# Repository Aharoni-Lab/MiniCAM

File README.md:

# MiniCAM
The MiniCAM is an open-source behaviroal camera for imaging freely behaving animals in behavioral and neuroscience experiments. The goal of the MiniCAM project is to provide an open-source, customizable, high-quality, and affordable alternative to using webcams or scientific USB cameras for behavioral imaging. The MiniCAM is powered and communicates over any commercial 50ohm coaxial cable minimizing the cabling that needs to run into the experimental environment. The coaxial cable connects the MiniDAQ to any version of UCLA Miniscope DAQs or MiniDAQs which then connects over USB3 to a host computer.

Using the [Miniscope Software](https://github.com/Aharoni-Lab/Miniscope-DAQ-QT-Software), multiple Miniscopes and MiniCAMs can be connected, streamed, and time-sync'ed recording simultaniously.

## MiniCAM Components
The MiniCAM consists of a custom printed circuit board (PCB), a 3D printed housing, an off the shelf M12 lens mount, a M12 camera lens, and an optional LED illumination ring. The PCB contains a 5MP CMOS image sensor, support electronics to power and serialize the imaging data, and an SMA coax connector. The image sensor can be configured through the Miniscope software and the optional LED illumination ring intensity can also be controlled through software. The MiniCAM runs at 50fps with 1024X768 resolution as the default configuration. Higher frame rate can be achieved by choosing smaller resolutions and higher resolution comes with lower frame rate.

## System Layout
The MiniCAM requires a UCLA Miniscope Data Acquisition (DAQ) board (connected over a 50ohm coaxial cable) and a host computer (connected over USB3) running the [Miniscope Software](https://github.com/Aharoni-Lab/Miniscope-DAQ-QT-Software) (or other third-party application that can stream UVC cameras and can communicate through a Miniscope DAQ). You can use any generation of Miniscope DAQ but you must update it with [the newest firmware](https://github.com/Aharoni-Lab/Miniscope-DAQ-Cypress-firmware). You can also use the cheaper and smaller version of the Miniscope DAQ called the MiniDAQ (open-source link coming soon). Once updated to the newest firmware, any Miniscope DAQ device will work with all Miniscope and MiniCAM devices. 

## M12 lenses and Coaxial Cables
Just like Miniscopes, the MiniCAM uses a 50Ohm coaxial cable for power, communication, and data. Any 50Ohm coax cable should work with the system. 

### M12 lenses
M12 lenses and M12 Mount Lens Holders are avaiable in Amazon (can be purchased at other places too). It can be handy to buy a M12 Lens Kit that comes with a range of M12 lenses for different view angles. We have been happy with the Arducam lens set which can be found on Amazon. If you are using the optional LED illumination ring or other nIR light source make sure to remove any IR filter located in the lens if applicable.

### Coaxial Cables
Any 50Ohm coaxial cable should be compatible with this system. It is not necessary to use the expensive, thin, flexible coax cables generally used with Miniscopes. The thicker the cable the longer length you can run (maxing out at around 10 to 15 meters). It generally is most convinient to get a coax cable with male SMA connectors on both ends to connect between the MiniCAM and MiniDAQ (or standard Miniscope DAQ).

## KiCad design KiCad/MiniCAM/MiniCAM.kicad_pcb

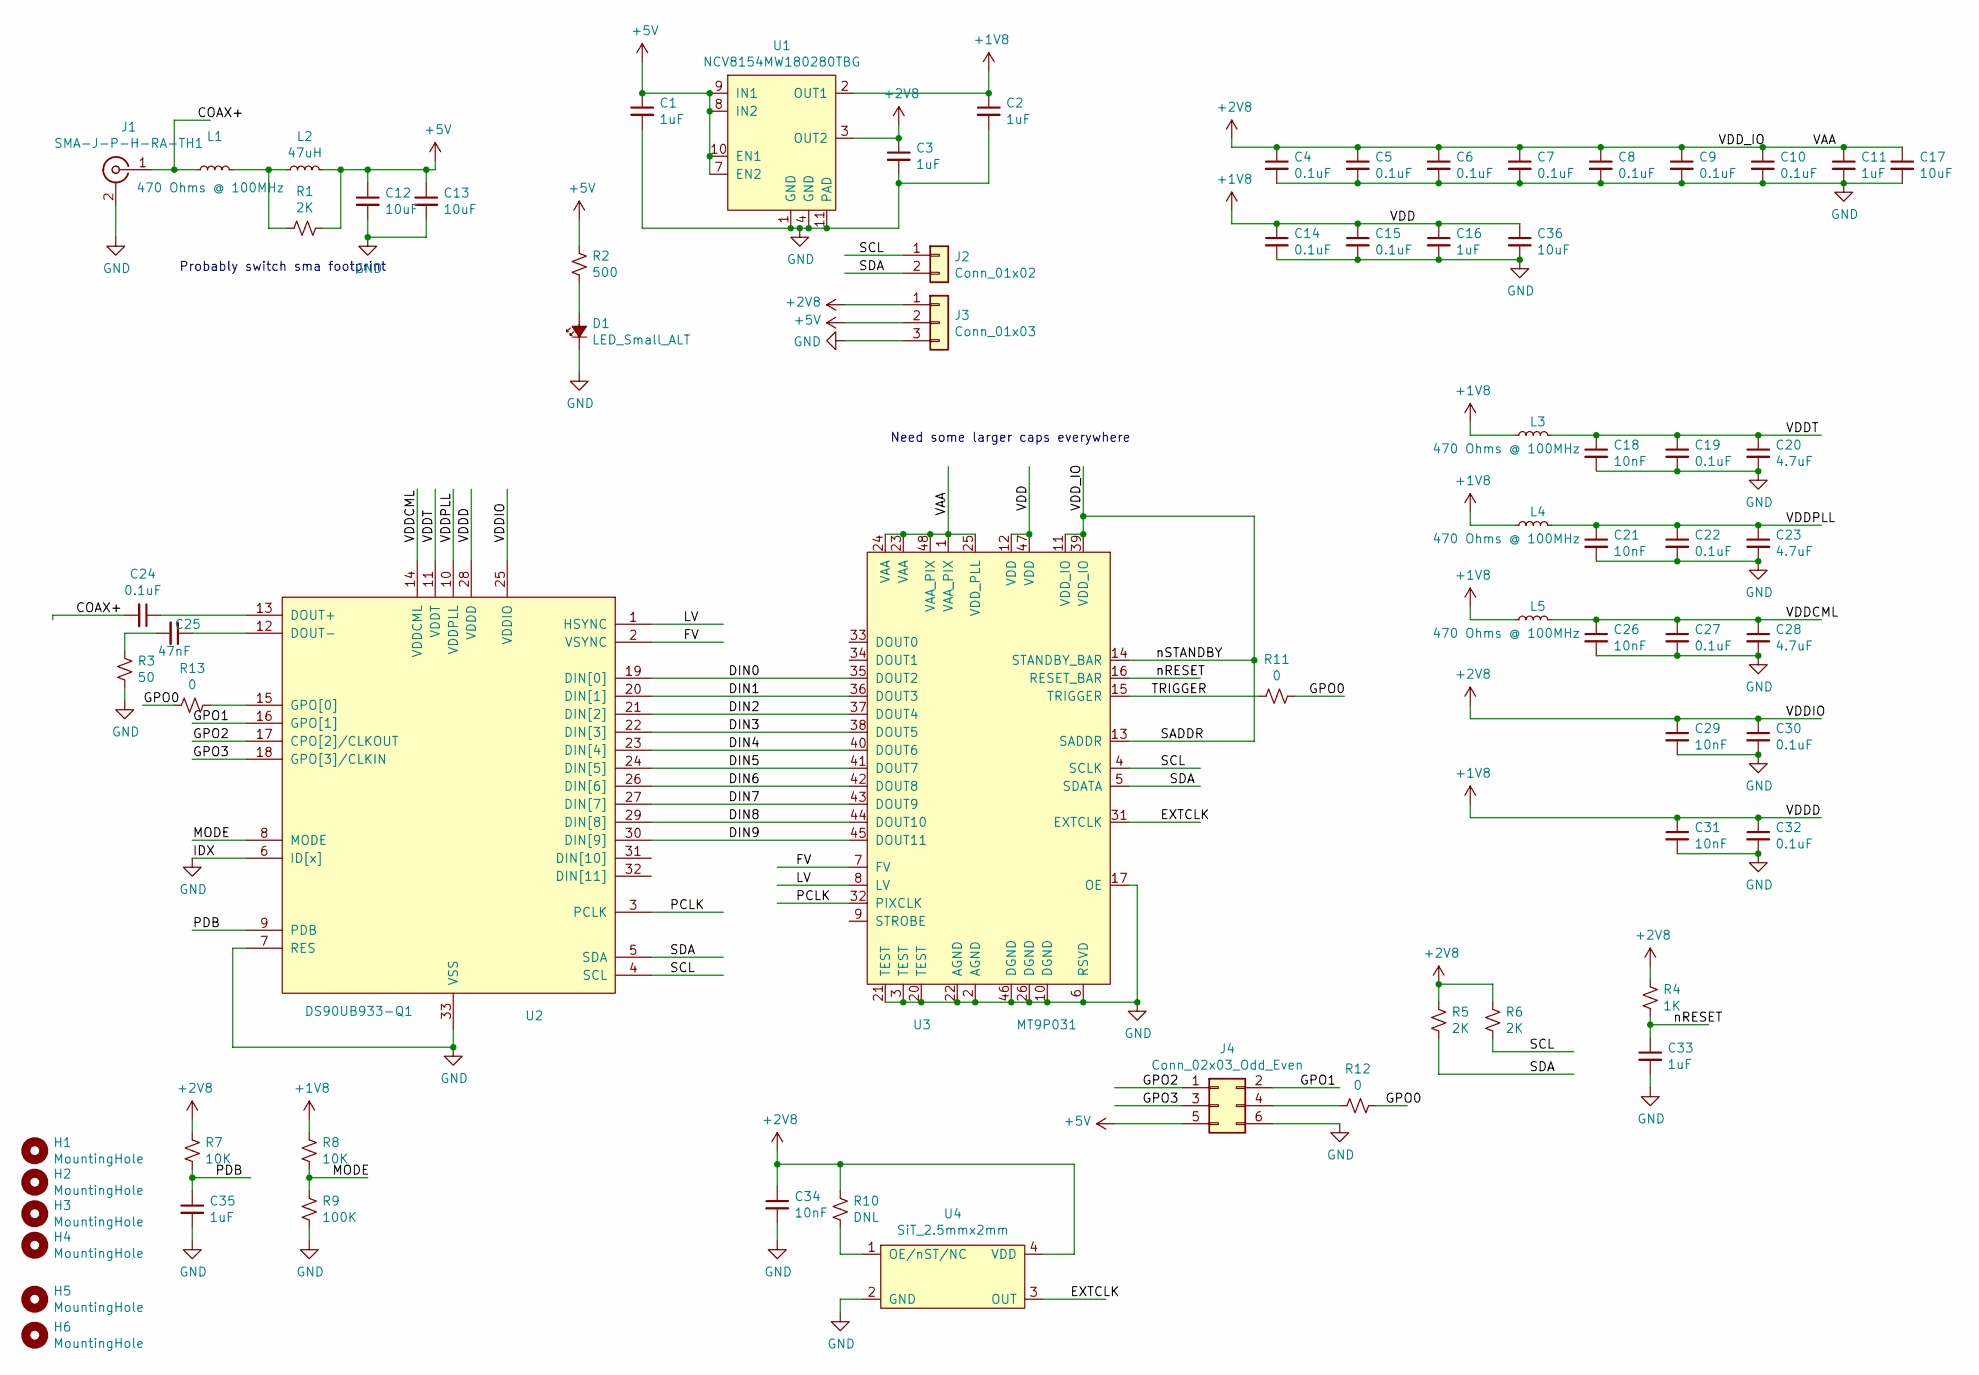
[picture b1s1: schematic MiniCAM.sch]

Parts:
C1, C2, C3, C11, C16, C33, C35: 1uF; C_0402_1005Metric_L; Part Number GRT155R61C105KE01D
C4, C5, C6, C7, C8, C9, C10, C14, C15, C19, C22, C24, C27, C30, C32: 0.1uF; C_0402_1005Metric_L; Part Number GCM155R71C104KA55J
C12, C13, C17, C36: 10uF; C_0603_1608Metric_L; Part Number GRM188R61A106KE69J
C18, C21, C26, C29, C31, C34: 10nF; C_0402_1005Metric_L; Part Number GCM155R71E103KA37D
C20, C23, C28: 4.7uF; C_0402_1005Metric_L; Part Number CC0402MRX5R6BB475
C25: 47nF; C_0402_1005Metric_L; Part Number GRM155R71A473KA01D
D1: LED_Small_ALT; LED_SC80X160X65L40L; Part Number LTST-C190KRKT
H1, H2, H3, H4, H5, H6: MountingHole; Conn_1x1_700_Circular_Pad; Part Number DNL
J1: SMA-J-P-H-RA-TH1; SMA_Amphenol_132134-10_Vertical; Part Number CONSMA001-SMD-G-T
J2: Conn_01x02; PinSocket_1x02_P1.27mm_Vertical; Part Number DNL
J3: Conn_01x03; PinSocket_1x03_P1.27mm_Vertical; Part Number DNL
J4: Conn_02x03_Odd_Even; PinSocket_2x03_P1.27mm_Horizontal; Part Number DNL
L1, L3, L4, L5: BLM18PG471SN1D; L_0603_1608Metric_L; Part Number BLM18PG471SN1D
L2: ADL3225V-470MT-TL000; L_1210_3225Metric_L; Part Number ADL3225V-470MT-TL000
R1, R5, R6: 2K; R_0402_1005Metric_ERJ_L; Part Number ERJ-2RKF2001X
R2: 500; R_0402_1005Metric_ERJ_L; Part Number ERJ-2RKF4990X
R3: 50; R_0402_1005Metric_ERJ_L; Part Number ERJ-2RKF49R9X
R4: 1K; R_0402_1005Metric_ERJ_L; Part Number ERJ-2GEJ102X
R7, R8: 10K; R_0402_1005Metric_ERJ_L; Part Number ERJ-2RKF1002X
R9: 100K; R_0402_1005Metric_ERJ_L; Part Number ERJ-2RKF1003X
R10: DNL; R_0402_1005Metric_ERJ_L; Part Number DNL
R11, R12, R13: 0; R_0402_1005Metric_ERJ_L; Part Number ERJ-2GE0R00X
U1: NCV8154MW180280TBG; DFN10_3x3_11P50_300X300X100L40X24T250X180N; Part Number NCV8154MW180280TBG
U2: DS90UB933-Q1; QFN_33_P50_500X500X80L40X24T310L; Part Number DS90UB913ATRTVTQ1
U3: MT9P031; iLCC48P70_1000X1000X135L80X40N; Part Number DNL
U4: SiT_2.5mmx2mm; OSC_CC250X200X80L70X75L; Part Number DNL

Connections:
+1V8: C2.1, C14.1, C15.1, C16.1, C31.1, C32.1, C36.1, L3.1, L4.1, L5.1, R8.1, U1.2 (OUT1), U2.28 (VDDD), U3.12 (VDD), U3.47 (VDD)
+2V8: C3.1, C4.1, C5.1, C6.1, C7.1, C8.1, C9.1, C10.1, C11.1, C17.1, C29.1, C30.1, C34.1, J3.1, R4.1, R5.1, R6.1, R7.1, R10.1, U1.3 (OUT2), U2.25 (VDDIO), U3.1 (VAA_PIX), U3.11 (VDD_IO), U3.13 (SADDR), U3.14 (STANDBY_BAR), U3.23 (VAA), U3.24 (VAA), U3.25 (VDD_PLL), U3.39 (VDD_IO), U3.48 (VAA_PIX), U4.4 (VDD)
+5V: C1.1, C12.1, C13.1, J3.2, J4.5, L2.2, R1.1, R2.1, U1.7 (EN2), U1.8 (IN2), U1.9 (IN1), U1.10 (EN1)
/COAX+: C24.2, J1.1 (In), L1.1
/DIN0: U2.19 (DIN[0]), U3.35 (DOUT2)
/DIN1: U2.20 (DIN[1]), U3.36 (DOUT3)
/DIN2: U2.21 (DIN[2]), U3.37 (DOUT4)
/DIN3: U2.22 (DIN[3]), U3.38 (DOUT5)
/DIN4: U2.23 (DIN[4]), U3.40 (DOUT6)
/DIN5: U2.24 (DIN[5]), U3.41 (DOUT7)
/DIN6: U2.26 (DIN[6]), U3.42 (DOUT8)
/DIN7: U2.27 (DIN[7]), U3.43 (DOUT9)
/DIN8: U2.29 (DIN[8]), U3.44 (DOUT10)
/DIN9: U2.30 (DIN[9]), U3.45 (DOUT11)
/EXTCLK: U3.31 (EXTCLK), U4.3 (OUT)
/FV: U2.2 (VSYNC), U3.7 (FV)
/GPO0: R11.1, R12.1, R13.2
/GPO1: J4.2, U2.16 (GPO[1])
/GPO2: J4.1, U2.17 (CPO[2]/CLKOUT)
/GPO3: J4.3, U2.18 (GPO[3]/CLKIN)
/LV: U2.1 (HSYNC), U3.8 (LV)
/MODE: R8.2, R9.1, U2.8 (MODE)
/PCLK: U2.3 (PCLK), U3.32 (PIXCLK)
/PDB: C35.1, R7.2, U2.9 (PDB)
/SCL: J2.1, R6.2, U2.4 (SCL), U3.4 (SCLK)
/SDA: J2.2, R5.2, U2.5 (SDA), U3.5 (SDATA)
/TRIGGER: R11.2, U3.15 (TRIGGER)
/VDDCML: C26.1, C27.1, C28.1, L5.2, U2.14 (VDDCML)
/VDDPLL: C21.1, C22.1, C23.1, L4.2, U2.10 (VDDPLL)
/VDDT: C18.1, C19.1, C20.1, L3.2, U2.11 (VDDT)
/nRESET: C33.1, R4.2, U3.16 (RESET_BAR)
GND: C1.2, C2.2, C3.2, C4.2, C5.2, C6.2, C7.2, C8.2, C9.2, C10.2, C11.2, C12.2, C13.2, C14.2, C15.2, C16.2, C17.2, C18.2, C19.2, C20.2, C21.2, C22.2, C23.2, C26.2, C27.2, C28.2, C29.2, C30.2, C31.2, C32.2, C33.2, C34.2, C35.2, C36.2, D1.1 (K), J1.2 (Ext), J3.3, J4.6, R3.2, R9.2, U1.1 (GND), U1.4 (GND), U1.11 (PAD), U2.6 (ID[x]), U2.7 (RES), U2.33 (VSS), U3.2 (AGND), U3.3 (TEST), U3.6 (RSVD), U3.10 (DGND), U3.17 (OE), U3.20 (TEST), U3.21 (TEST), U3.22 (AGND), U3.26 (DGND), U3.46 (DGND), U4.2 (GND)
unnamed: C24.1, U2.13 (DOUT+)
unnamed: C25.1, U2.12 (DOUT-)
unnamed: C25.2, R3.1
unnamed: D1.2 (A), R2.2
unnamed: J4.4, R12.2
unnamed: L1.2, L2.1, R1.2
unnamed: R10.2, U4.1 (OE/nST/NC)
unnamed: R13.1, U2.15 (GPO[0])

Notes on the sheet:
Need some larger caps everywhere
Probably switch sma footprint

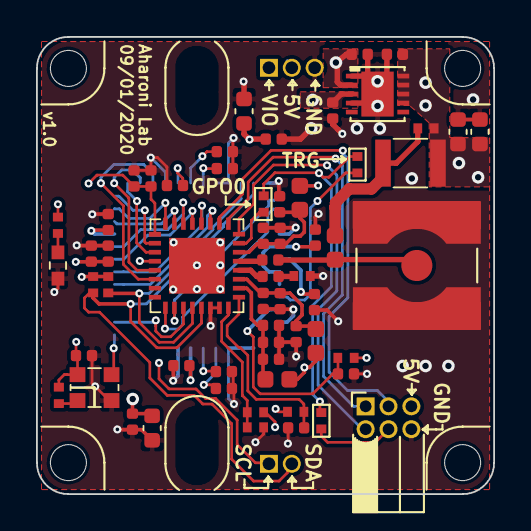
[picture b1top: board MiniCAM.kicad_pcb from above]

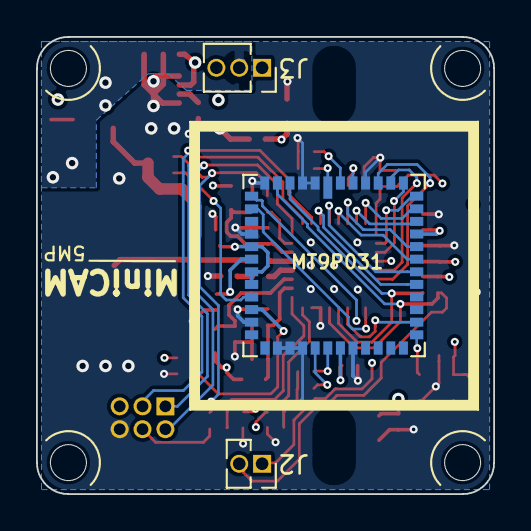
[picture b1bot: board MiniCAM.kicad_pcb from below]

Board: 4 copper layers, 25.4 x 25.4 mm, 69 parts (3 on the bottom side), 40 nets.

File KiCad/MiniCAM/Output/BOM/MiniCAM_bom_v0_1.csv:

Component,Description,Part,References,Value,Footprint,Quantity Per PCB,Datasheet,Part Number,Note,Size,LCSC Part #
1,"Unpolarized capacitor, small symbol",C_Small,C4 C5 C6 C7 C8 C9 C10 C14 C15 C19 C22 C24 C27 C30 C32,0.1uF,C_0402_1005Metric_L,15,~,GCM155R71C104KA55J,,,
2,"Unpolarized capacitor, small symbol",C_Small,C18 C21 C26 C29 C31 C34,10nF,C_0402_1005Metric_L,6,~,GCM155R71E103KA37D,,,
3,"Unpolarized capacitor, small symbol",C_Small,C12 C13 C17 C36,10uF,C_0603_1608Metric_L,4,~,GRM188R61A106KE69J,,,
4,"Unpolarized capacitor, small symbol",C_Small,C1 C2 C3 C11 C16 C33 C35,1uF,C_0402_1005Metric_L,7,~,GRT155R61C105KE01D,,,C363938
5,"Unpolarized capacitor, small symbol",C_Small,C20 C23 C28,4.7uF,C_0402_1005Metric_L,3,~,CC0402MRX5R6BB475,,,
6,"Unpolarized capacitor, small symbol",C_Small,C25,47nF,C_0402_1005Metric_L,1,~,GRM155R71A473KA01D,,,
7,"Light emitting diode, small symbol, filled shape",LED_Small_ALT,D1,LED_Small_ALT,LED_SC80X160X65L40L,1,~,LTST-C190KRKT,,,C2286
11,CONN SMA JACK R/A 50 OHM PCB,SMA-J-P-H-RA-TH1,J1,SMA-J-P-H-RA-TH1,SMA_Amphenol_132134-10_Vertical,1,http://suddendocs.samtec.com/catalog_english/sma.pdf,CONSMA001-SMD-G-T,,,
12,FIXED IND 47UH 500MA 900 MOHM,ADL3225V-470MT-TL000,L2,ADL3225V-470MT-TL000,L_1210_3225Metric_L,1,https://product.tdk.com/info/en/catalog/datasheets/inductor_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,ADL3225V-470MT-TL000,47uH,1210, C435260
13,FERRITE BEAD 470 OHM 0603 1LN,BLM18PG471SN1D,L1 L3 L4 L5,BLM18PG471SN1D,L_0603_1608Metric_L,4,https://www.murata.com/en-us/products/productdata/8796738650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,BLM18PG471SN1D,470 Ohms @ 100MHz,603,C97853
14,"Resistor, small US symbol",R_Small_US,R11 R12 R13,0,R_0402_1005Metric_ERJ_L,3,~,ERJ-2GE0R00X,,,
15,"Resistor, small US symbol",R_Small_US,R9,100K,R_0402_1005Metric_ERJ_L,1,~,ERJ-2RKF1003X,,,
16,"Resistor, small US symbol",R_Small_US,R7 R8,10K,R_0402_1005Metric_ERJ_L,2,~,ERJ-2RKF1002X,,,
17,"Resistor, small US symbol",R_Small_US,R4,1K,R_0402_1005Metric_ERJ_L,1,~,ERJ-2GEJ102X,,,
18,"Resistor, small US symbol",R_Small_US,R1 R5 R6,2K,R_0402_1005Metric_ERJ_L,3,~,ERJ-2RKF2001X,,,
19,"Resistor, small US symbol",R_Small_US,R3,50,R_0402_1005Metric_ERJ_L,1,~,ERJ-2RKF49R9X,,,C441726
20,"Resistor, small US symbol",R_Small_US,R2,500,R_0402_1005Metric_ERJ_L,1,~,ERJ-2RKF4990X,,,C137970
21,IC SERIALIZER FPD-LINK 32WQFN,DS90UB933-Q1,U2,DS90UB933-Q1,QFN_33_P50_500X500X80L40X24T310L,1,http://www.ti.com/lit/ds/symlink/ds90ub933-q1.pdf,DS90UB913ATRTVTQ1,,,
23,Voltage Regulator - Dual 300mA fixed,NCV8154,U1,NCV8154MW180280TBG,DFN10_3x3_11P50_300X300X100L40X24T250X180N,1,https://www.onsemi.com/pub/Collateral/NCV8154-D.PDF,NCV8154MW180280TBG,,,
,,,,,,,,,,,
,,,,,,,,,,,
,,,,,,,,,,,
,,,,,,,,,,,
,,,,,,,,,,,
Component Groups:,25,,,,,,,,,,
Component Count:,63,,,,,,,,,,
Fitted Components:,62,,,,,,,,,,
Number of PCBs:,1,,,,,,,,,,
Total components:,62,,,,,,,,,,
Schematic Version:,,,,,,,,,,,
Schematic Date:,,,,,,,,,,,
PCB Variant:,default,,,,,,,,,,
BoM Date:,7/21/2020 23:12,,,,,,,,,,
Schematic Source:,C:\Users\DBAharoni\Documents\Projects\MiniCAM\KiCad\MiniCAM\MiniCAM.sch,,,,,,,,,,
KiCad Version:,Eeschema (5.1.5)-3,,,,,,,,,,

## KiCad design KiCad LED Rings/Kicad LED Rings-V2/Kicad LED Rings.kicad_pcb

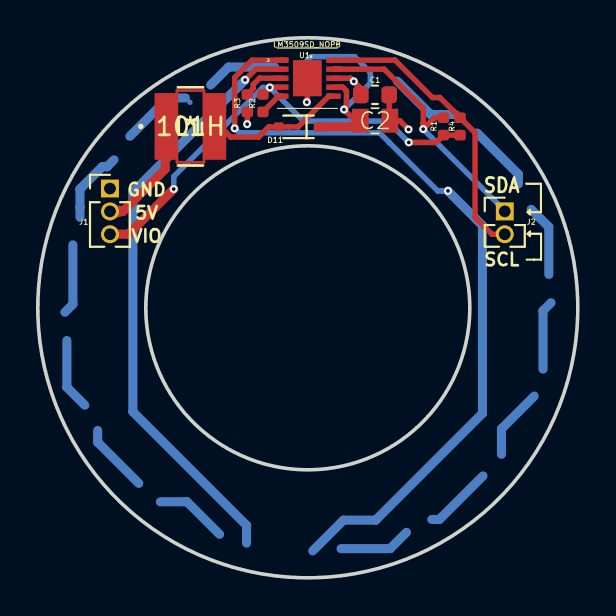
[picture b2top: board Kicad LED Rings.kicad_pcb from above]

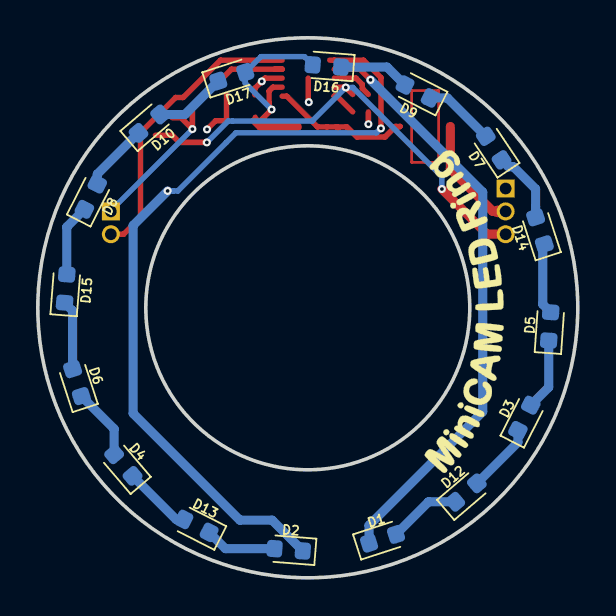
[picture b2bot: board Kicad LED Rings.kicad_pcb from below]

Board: 4 copper layers, 30.0 x 30.0 mm, 27 parts (16 on the bottom side), 25 nets.

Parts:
C1: 1uF; C_0603_1608Metric
C2: 2.2uF; C_0805_2012Metric_L
D1, D2, D3, D4, D5, D6, D7, D8, D9, D10, D12, D13, D14, D15, D16, D17: LED_Small_ALT; LED_0603_1608Metric
D11: D_Schottky; SOD323(F)
J1: Conn_01x02_Female; PinHeader_1x03_P1.27mm_Vertical
J2: Conn_01x02_Male; PinHeader_1x02_P1.27mm_Vertical
L1: 10uH; NRS4012T100MDGJ
R1, R4: 3K; R_0402_1005Metric
R2, R3: 9.5k; R_0402_1005Metric
U1: LM3509SD_NOPB; LM3509SD&slash_NOPB

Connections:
+2V8: J1.3, R1.2, R2.1, R4.2, U1.4
+5V: C1.2, J1.2, L1.1, U1.8
GND: C1.1, C2.1, J1.1, R3.1, U1.11
unnamed: D1.1, U1.2
unnamed: D1.2, D12.1
unnamed: D2.1, U1.1
unnamed: D3.2, D5.1
unnamed: D4.2, D6.1
unnamed: D7.2, D9.1
unnamed: D8.2, D10.1
unnamed: D10.2, D17.1
unnamed: D11.2, L1.2, U1.6
unnamed: D3.1, D12.2
unnamed: D2.2, D13.1
unnamed: D4.1, D13.2
unnamed: D5.2, D14.1
unnamed: D7.1, D14.2
unnamed: D6.2, D15.1
unnamed: D8.1, D15.2
unnamed: D9.2, D16.1
unnamed: R2.2, U1.5
unnamed: R3.2, U1.3
OVP: C2.2, D11.1, D16.2, D17.2, U1.7
SCL: J2.2, R4.1, U1.10
SDA: J2.1, R1.1, U1.9

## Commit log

2020-07-17 Do initial schematic and import into pcb layout
2020-07-18 Finish initial schematic, layout, and routing.
2020-07-18 Switch 2 and 3 headers from pins to sockets. Generate STEP file.
2020-07-18 Switch 2 and 3 socket headers for longer 3D model ones. Generate new STEP.
2020-07-19 Move LED ring headers to a consistent 4mm x 1mm spacing from center on lens.
2020-07-19 Added LED Ring PCB
    1. Made the led rings closer to outer edge;
    2. Added text for GND, 5V, VIO, SDA, and SCL;
    3. Added text MiniCAM LED Ring;
    4. Shfited the male pin headers to fit the female pin headers on Daniel's behavior camera pcb;
    5. made the center hole of led ring pcb bigger for bigger m12 lens holder.
2020-07-19 LED Ring PCB
    Roated the MiniCAM LED Ring by 90 degrees.
2020-07-20 Add connection to TRIG pin of sensor along with 0 resistors
2020-07-20 Forgot to save schematic for last commit. Here it is.
2020-07-20 Updated LED ring pcb
    Changed Rset from 12k to 9.5k which can generate 25mA current for LEDs
2020-07-22 Generate BOM, PnP, Gerbers. Check and correct DRC errors. v0.1
2020-07-30 Updated LED Ring PCB board
    updated BOM;
    updated Gerber;
2020-07-30 Updated LED ring PCB
    added part NO. of LM3509SD_NOPB
2020-07-30 Updated LED Ring PCB
    Changed '10uF 0603 25V' to '10uF 1210 50V'
2020-07-30 Updated LED ring PCB Board
    Changed 10UF 0603 to 1210 50V: C1210C106K5RACTU
2020-07-30 Updated LED Ring PCB
2020-07-30 Updated LED ring PCB
    Added LED Ring PCB logo
2020-07-31 Upldated LED ring PCB
    Changed 10uF Cout to C2012X5R1E225M125AC;
    Changed 10uH inductor to NRS4012T100MDGJ;
2020-07-31 Updated LED ring PCB
    Removed the vias off the pads
2020-08-01 Modified PCB layout
2020-08-01 Change file naming. Generate GERBERS.
2020-08-03 Updated LFOV miniscope PCB
    updated Gerber file
2020-09-01 Upldated MiniCAM
    Removed the short footprint of 10uH inductor NRS4012T100MDGJ;
    Corrected the wroing footprint of 10uH inductor and saved the corrected footprint as 'NRS4012T100MDGJ_Corrected_09012020' in C:\Users\Changliang Guo\Desktop\GitHub\MiniCAM\KiCad LED Rings\10uH Induct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
2020-09-02 Correct minor error on top silk screen. Change to rev v1.0
2020-09-02 Updated LED ring pcb
    Corrected the messed up schematics and footprints
    Regenerated the Gerber files, position files, and drill files
2020-09-02 updated led ring pcb board
2020-09-02 Updated LED ring pcb
    regenerated Gerber, position, and drl files
2020-09-08 Update output files and check part numbers for v1.0 fabrication
2021-06-14 Update readme and add img and housing files
2021-06-14 Make schematic pdfs
2021-06-25 Clean up MiniCAM KiCad schematic

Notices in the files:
parts and their libraries:
Copyright 2016 Accelerated Designs. All rights reserved.
